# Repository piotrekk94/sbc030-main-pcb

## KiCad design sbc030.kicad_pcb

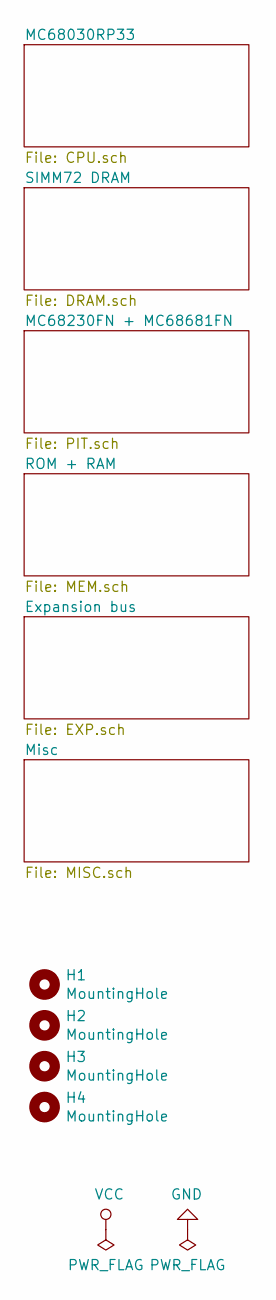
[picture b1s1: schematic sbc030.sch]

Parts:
H1, H2, H3, H4: MountingHole; MountingHole_3.2mm_M3_Pad

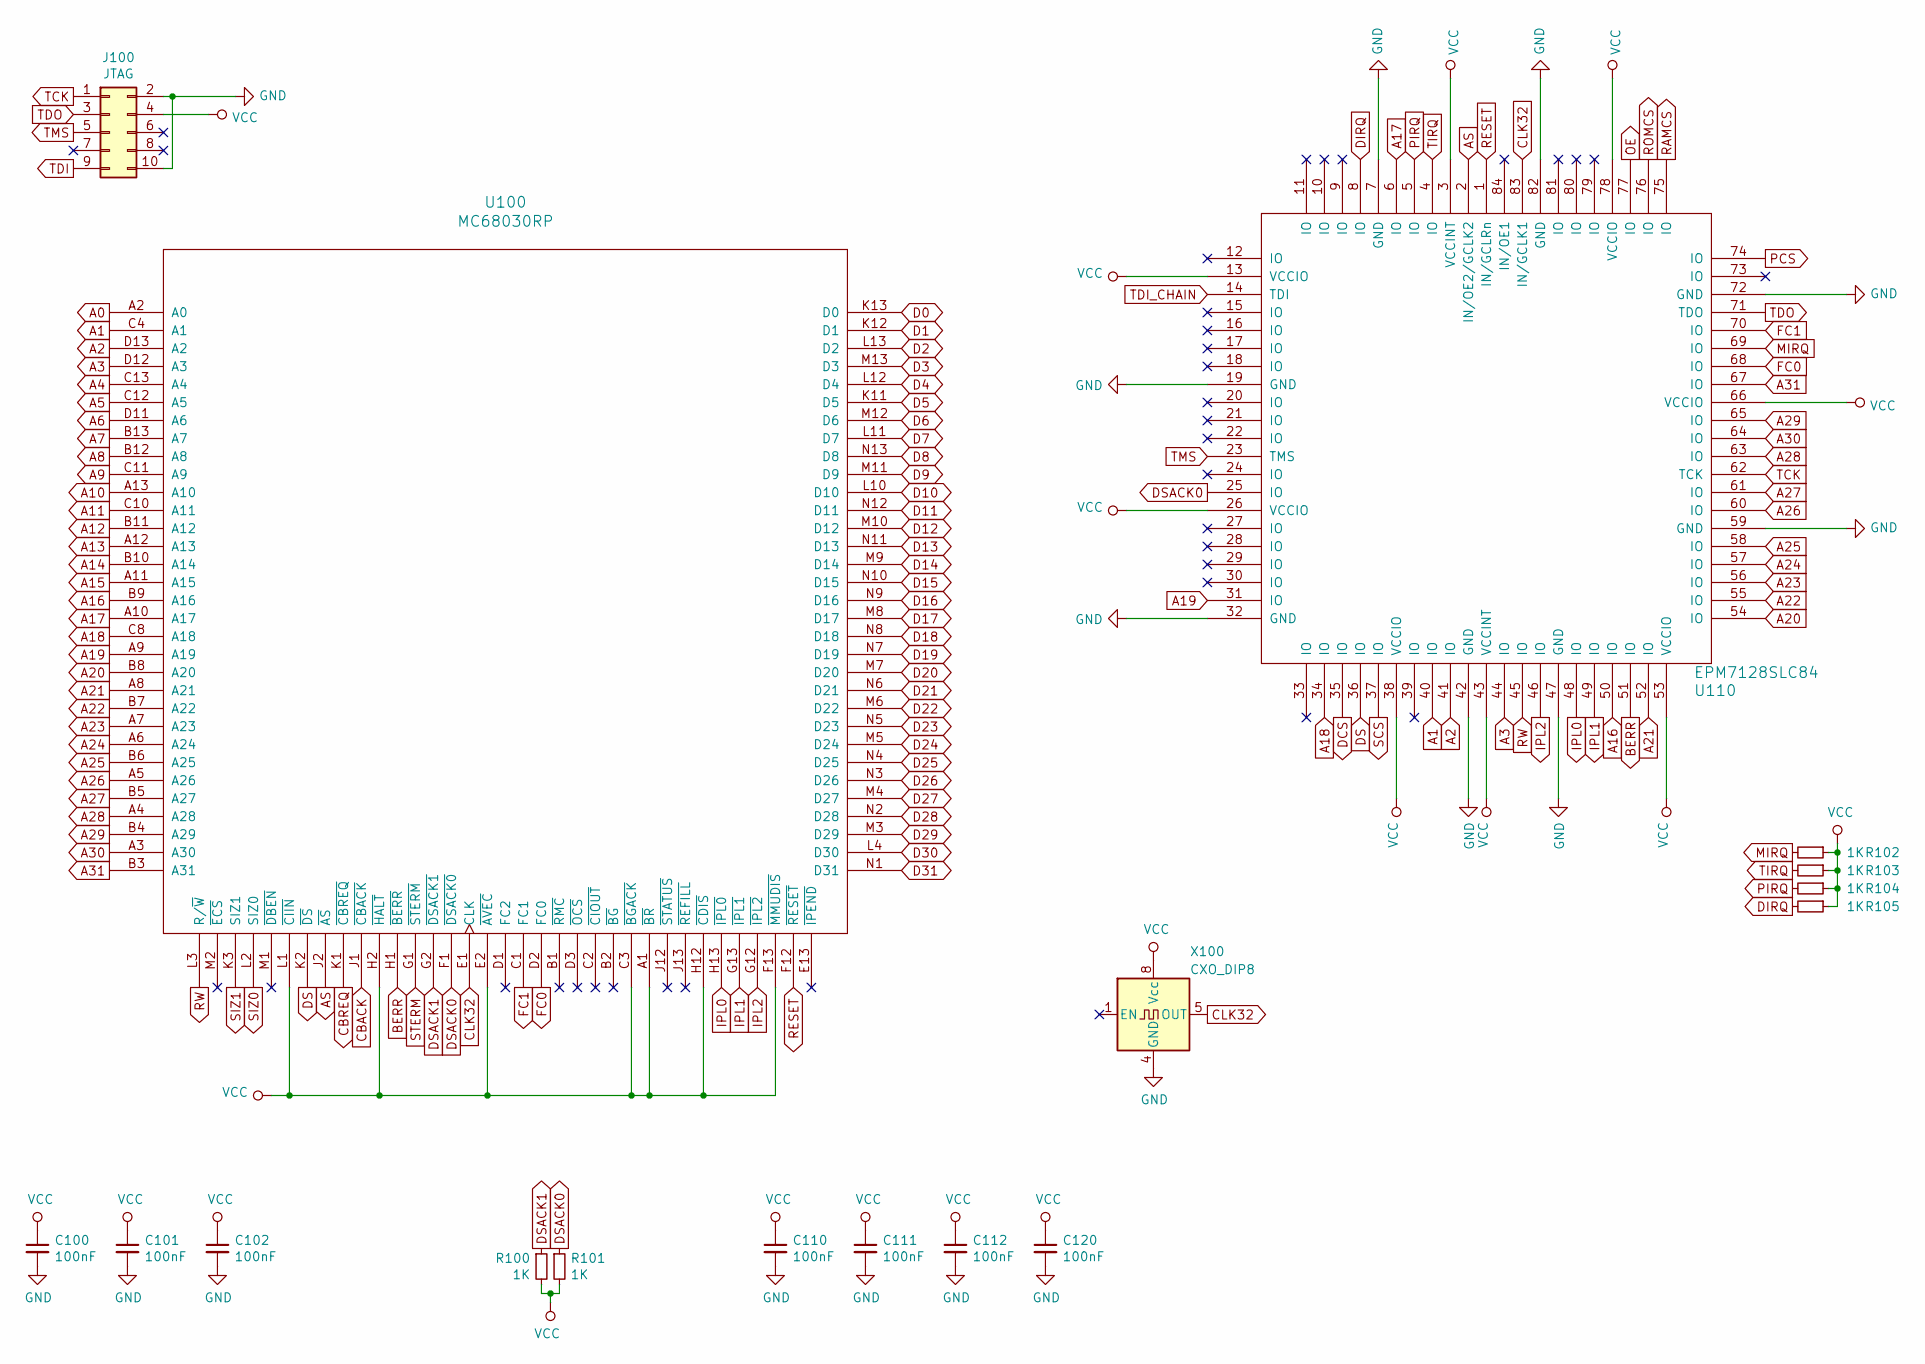
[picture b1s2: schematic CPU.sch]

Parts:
C100, C101, C102, C110, C111, C112, C120: 100nF; C_0603_1608Metric_Pad1.05x0.95mm_HandSolder
J100: JTAG; PinHeader_2x05_P2.54mm_Vertical
R100, R101, R102, R103, R104, R105: 1K; R_0603_1608Metric_Pad1.05x0.95mm_HandSolder
U100: MC68030RP; PGA128
U110: EPM7128SLC84; PLCC-84_THT-Socket
X100: CXO_DIP8; Oscillator_DIP-8

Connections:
A0: U100.A2 (A0); also elsewhere on the board
A1: U100.C4 (A1), U110.40 (IO); also elsewhere on the board
A2: U100.D13 (A2), U110.41 (IO); also elsewhere on the board
A3: U100.D12 (A3), U110.44 (IO); also elsewhere on the board
A4: U100.C13 (A4); also elsewhere on the board
A5: U100.C12 (A5); also elsewhere on the board
A6: U100.D11 (A6); also elsewhere on the board
A7: U100.B13 (A7); also elsewhere on the board
A8: U100.B12 (A8); also elsewhere on the board
A9: U100.C11 (A9); also elsewhere on the board
A10: U100.A13 (A10); also elsewhere on the board
A11: U100.C10 (A11); also elsewhere on the board
A12: U100.B11 (A12); also elsewhere on the board
A13: U100.A12 (A13); also elsewhere on the board
A14: U100.B10 (A14); also elsewhere on the board
A15: U100.A11 (A15); also elsewhere on the board
A16: U100.B9 (A16), U110.50 (IO); also elsewhere on the board
A17: U100.A10 (A17), U110.6 (IO); also elsewhere on the board
A18: U100.C8 (A18), U110.34 (IO); also elsewhere on the board
A19: U100.A9 (A19), U110.31 (IO); also elsewhere on the board
A20: U100.B8 (A20), U110.54 (IO); also elsewhere on the board
A21: U100.A8 (A21), U110.52 (IO); also elsewhere on the board
A22: U100.B7 (A22), U110.55 (IO); also elsewhere on the board
A23: U100.A7 (A23), U110.56 (IO); also elsewhere on the board
A24: U100.A6 (A24), U110.57 (IO); also elsewhere on the board
A25: U100.B6 (A25), U110.58 (IO); also elsewhere on the board
A26: U100.A5 (A26), U110.60 (IO); also elsewhere on the board
A27: U100.B5 (A27), U110.61 (IO); also elsewhere on the board
A28: U100.A4 (A28), U110.63 (IO); also elsewhere on the board
A29: U100.B4 (A29), U110.65 (IO); also elsewhere on the board
A30: U100.A3 (A30), U110.64 (IO); also elsewhere on the board
A31: U100.B3 (A31), U110.67 (IO); also elsewhere on the board
AS: U100.J2 (~AS), U110.2 (IN/OE2/GCLK2); also elsewhere on the board
BERR: U100.H1 (~BERR), U110.51 (IO)
CBACK: U100.J1 (~CBACK); also elsewhere on the board
CBREQ: U100.K1 (~CBREQ); also elsewhere on the board
CLK32: U100.E1 (CLK), U110.83 (IN/GCLK1), X100.5 (OUT); also elsewhere on the board
D0: U100.K13 (D0); also elsewhere on the board
D1: U100.K12 (D1); also elsewhere on the board
D2: U100.L13 (D2); also elsewhere on the board
D3: U100.M13 (D3); also elsewhere on the board
D4: U100.L12 (D4); also elsewhere on the board
D5: U100.K11 (D5); also elsewhere on the board
D6: U100.M12 (D6); also elsewhere on the board
D7: U100.L11 (D7); also elsewhere on the board
D8: U100.N13 (D8); also elsewhere on the board
D9: U100.M11 (D9); also elsewhere on the board
D10: U100.L10 (D10); also elsewhere on the board
D11: U100.N12 (D11); also elsewhere on the board
D12: U100.M10 (D12); also elsewhere on the board
D13: U100.N11 (D13); also elsewhere on the board
D14: U100.M9 (D14); also elsewhere on the board
D15: U100.N10 (D15); also elsewhere on the board
D16: U100.N9 (D16); also elsewhere on the board
D17: U100.M8 (D17); also elsewhere on the board
D18: U100.N8 (D18); also elsewhere on the board
D19: U100.N7 (D19); also elsewhere on the board
D20: U100.M7 (D20); also elsewhere on the board
D21: U100.N6 (D21); also elsewhere on the board
D22: U100.M6 (D22); also elsewhere on the board
D23: U100.N5 (D23); also elsewhere on the board
D24: U100.M5 (D24); also elsewhere on the board
D25: U100.N4 (D25); also elsewhere on the board
D26: U100.N3 (D26); also elsewhere on the board
D27: U100.M4 (D27); also elsewhere on the board
D28: U100.N2 (D28); also elsewhere on the board
D29: U100.M3 (D29); also elsewhere on the board
D30: U100.L4 (D30); also elsewhere on the board
D31: U100.N1 (D31); also elsewhere on the board
DCS: U110.35 (IO); also elsewhere on the board
DIRQ: R105.2, U110.8 (IO); also elsewhere on the board
DS: U100.K2 (~DS), U110.36 (IO); also elsewhere on the board
DSACK0: R101.1, U100.F1 (~DSACK0), U110.25 (IO); also elsewhere on the board
DSACK1: R100.1, U100.G2 (~DSACK1); also elsewhere on the board
FC0: U100.D2 (FC0), U110.68 (IO); also elsewhere on the board
FC1: U100.C1 (FC1), U110.70 (IO); also elsewhere on the board
GND: C100.2, C101.2, C102.2, C110.2, C111.2, C112.2, C120.2, J100.2, J100.10, U100.C5 (GND), U100.C7 (GND), U100.C9 (GND), U100.E3 (GND), U100.E11 (GND), U100.F3 (GND), U100.G3 (GND), U100.G11 (GND), U100.J3 (GND), U100.J11 (GND), U100.L5 (GND), U100.L7 (GND), U100.L8 (GND), U100.L9 (GND), U110.7 (GND), U110.19 (GND), U110.32 (GND), U110.42 (GND), U110.47 (GND), U110.59 (GND), U110.72 (GND), U110.82 (GND), X100.4 (GND); also elsewhere on the board
IPL0: U100.H13 (~IPL0), U110.48 (IO)
IPL1: U100.G13 (~IPL1), U110.49 (IO)
IPL2: U100.G12 (~IPL2), U110.46 (IO)
MIRQ: R102.2, U110.69 (IO); also elsewhere on the board
OE: U110.77 (IO); also elsewhere on the board
PCS: U110.74 (IO); also elsewhere on the board
PIRQ: R104.2, U110.5 (IO); also elsewhere on the board
RAMCS: U110.75 (IO); also elsewhere on the board
RESET: U100.F12 (~RESET), U110.1 (IN/GCLRn); also elsewhere on the board
ROMCS: U110.76 (IO); also elsewhere on the board
RW: U100.L3 (R/~W), U110.45 (IO); also elsewhere on the board
SCS: U110.37 (IO); also elsewhere on the board
SIZ0: U100.L2 (SIZ0); also elsewhere on the board
SIZ1: U100.K3 (SIZ1); also elsewhere on the board
STERM: U100.G1 (~STERM); also elsewhere on the board
TCK: J100.1, U110.62 (TCK); also elsewhere on the board
TDI: J100.9; also elsewhere on the board
TDI_CHAIN: U110.14 (TDI); also elsewhere on the board
TDO: J100.3, U110.71 (TDO)
TIRQ: R103.2, U110.4 (IO); also elsewhere on the board
TMS: J100.5, U110.23 (TMS); also elsewhere on the board
VCC: C100.1, C101.1, C102.1, C110.1, C111.1, C112.1, C120.1, J100.4, R100.2, R101.2, R102.1, R103.1, R104.1, R105.1, U100.A1 (~BR), U100.C3 (~BGACK), U100.C6 (VCC), U100.D4 (VCC), U100.D10 (VCC), U100.E2 (~AVEC), U100.F2 (VCC), U100.F11 (VCC), U100.F13 (~MMUDIS), U100.H2 (~HALT), U100.H3 (VCC), U100.H11 (VCC), U100.H12 (~CDIS), U100.K4 (VCC), U100.K10 (VCC), U100.L1 (~CIIN), U100.L6 (VCC), U110.3 (VCCINT), U110.13 (VCCIO), U110.26 (VCCIO), U110.38 (VCCIO), U110.43 (VCCINT), U110.53 (VCCIO), U110.66 (VCCIO), U110.78 (VCCIO), X100.8 (Vcc); also elsewhere on the board

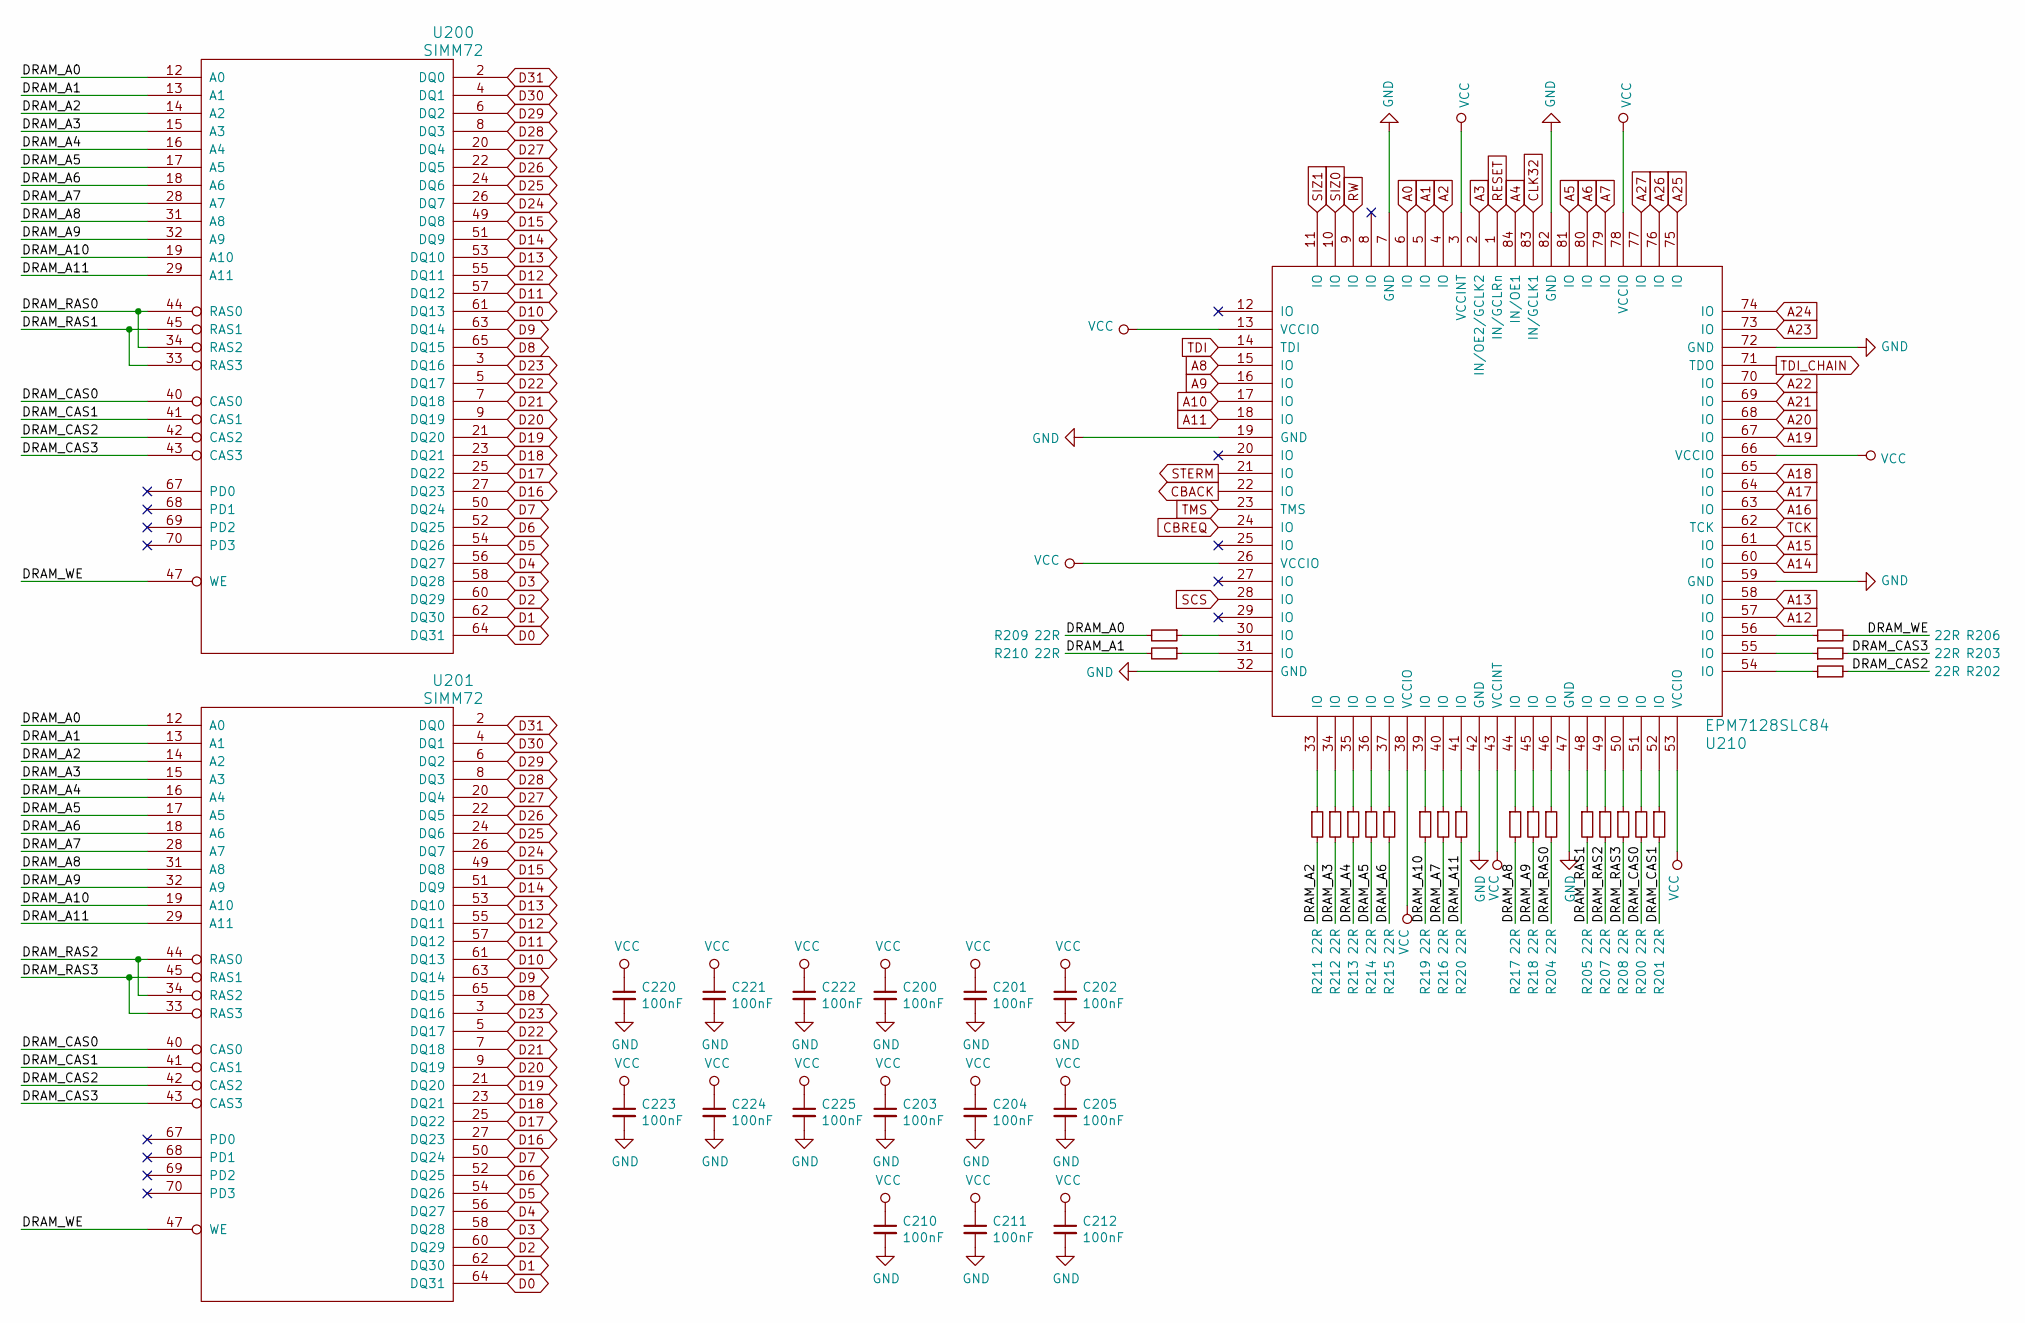
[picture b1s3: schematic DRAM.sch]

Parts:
C200, C201, C202, C203, C204, C205, C210, C211, C212, C220, C221, C222, C223, C224, C225: 100nF; C_0603_1608Metric_Pad1.05x0.95mm_HandSolder
R200, R201, R202, R203, R204, R205, R206, R207, R208, R209, R210, R211, R212, R213, R214, R215, R216, R217, R218, R219, R220: 22R; R_0603_1608Metric_Pad1.05x0.95mm_HandSolder
U200, U201: SIMM72; SIM72
U210: EPM7128SLC84; PLCC-84_THT-Socket

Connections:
/SIMM72 DRAM/DRAM_A0: R209.2, U200.12 (A0), U201.12 (A0)
/SIMM72 DRAM/DRAM_A1: R210.2, U200.13 (A1), U201.13 (A1)
/SIMM72 DRAM/DRAM_A2: R211.2, U200.14 (A2), U201.14 (A2)
/SIMM72 DRAM/DRAM_A3: R212.2, U200.15 (A3), U201.15 (A3)
/SIMM72 DRAM/DRAM_A4: R213.2, U200.16 (A4), U201.16 (A4)
/SIMM72 DRAM/DRAM_A5: R214.2, U200.17 (A5), U201.17 (A5)
/SIMM72 DRAM/DRAM_A6: R215.2, U200.18 (A6), U201.18 (A6)
/SIMM72 DRAM/DRAM_A7: R216.2, U200.28 (A7), U201.28 (A7)
/SIMM72 DRAM/DRAM_A8: R217.2, U200.31 (A8), U201.31 (A8)
/SIMM72 DRAM/DRAM_A9: R218.2, U200.32 (A9), U201.32 (A9)
/SIMM72 DRAM/DRAM_A10: R219.2, U200.19 (A10), U201.19 (A10)
/SIMM72 DRAM/DRAM_A11: R220.2, U200.29 (A11), U201.29 (A11)
/SIMM72 DRAM/DRAM_CAS0: R200.2, U200.40 (CAS0), U201.40 (CAS0)
/SIMM72 DRAM/DRAM_CAS1: R201.2, U200.41 (CAS1), U201.41 (CAS1)
/SIMM72 DRAM/DRAM_CAS2: R202.2, U200.42 (CAS2), U201.42 (CAS2)
/SIMM72 DRAM/DRAM_CAS3: R203.2, U200.43 (CAS3), U201.43 (CAS3)
/SIMM72 DRAM/DRAM_RAS0: R204.2, U200.34 (RAS2), U200.44 (RAS0)
/SIMM72 DRAM/DRAM_RAS1: R205.2, U200.33 (RAS3), U200.45 (RAS1)
/SIMM72 DRAM/DRAM_RAS2: R207.2, U201.34 (RAS2), U201.44 (RAS0)
/SIMM72 DRAM/DRAM_RAS3: R208.2, U201.33 (RAS3), U201.45 (RAS1)
/SIMM72 DRAM/DRAM_WE: R206.2, U200.47 (WE), U201.47 (WE)
A0: U210.6 (IO); also elsewhere on the board
A1: U210.5 (IO); also elsewhere on the board
A2: U210.4 (IO); also elsewhere on the board
A3: U210.2 (IN/OE2/GCLK2); also elsewhere on the board
A4: U210.84 (IN/OE1); also elsewhere on the board
A5: U210.81 (IO); also elsewhere on the board
A6: U210.80 (IO); also elsewhere on the board
A7: U210.79 (IO); also elsewhere on the board
A8: U210.15 (IO); also elsewhere on the board
A9: U210.16 (IO); also elsewhere on the board
A10: U210.17 (IO); also elsewhere on the board
A11: U210.18 (IO); also elsewhere on the board
A12: U210.57 (IO); also elsewhere on the board
A13: U210.58 (IO); also elsewhere on the board
A14: U210.60 (IO); also elsewhere on the board
A15: U210.61 (IO); also elsewhere on the board
A16: U210.63 (IO); also elsewhere on the board
A17: U210.64 (IO); also elsewhere on the board
A18: U210.65 (IO); also elsewhere on the board
A19: U210.67 (IO); also elsewhere on the board
A20: U210.68 (IO); also elsewhere on the board
A21: U210.69 (IO); also elsewhere on the board
A22: U210.70 (IO); also elsewhere on the board
A23: U210.73 (IO); also elsewhere on the board
A24: U210.74 (IO); also elsewhere on the board
A25: U210.75 (IO); also elsewhere on the board
A26: U210.76 (IO); also elsewhere on the board
A27: U210.77 (IO); also elsewhere on the board
CBACK: U210.22 (IO); also elsewhere on the board
CBREQ: U210.24 (IO); also elsewhere on the board
CLK32: U210.83 (IN/GCLK1); also elsewhere on the board
D0: U200.64 (DQ31), U201.64 (DQ31); also elsewhere on the board
D1: U200.62 (DQ30), U201.62 (DQ30); also elsewhere on the board
D2: U200.60 (DQ29), U201.60 (DQ29); also elsewhere on the board
D3: U200.58 (DQ28), U201.58 (DQ28); also elsewhere on the board
D4: U200.56 (DQ27), U201.56 (DQ27); also elsewhere on the board
D5: U200.54 (DQ26), U201.54 (DQ26); also elsewhere on the board
D6: U200.52 (DQ25), U201.52 (DQ25); also elsewhere on the board
D7: U200.50 (DQ24), U201.50 (DQ24); also elsewhere on the board
D8: U200.65 (DQ15), U201.65 (DQ15); also elsewhere on the board
D9: U200.63 (DQ14), U201.63 (DQ14); also elsewhere on the board
D10: U200.61 (DQ13), U201.61 (DQ13); also elsewhere on the board
D11: U200.57 (DQ12), U201.57 (DQ12); also elsewhere on the board
D12: U200.55 (DQ11), U201.55 (DQ11); also elsewhere on the board
D13: U200.53 (DQ10), U201.53 (DQ10); also elsewhere on the board
D14: U200.51 (DQ9), U201.51 (DQ9); also elsewhere on the board
D15: U200.49 (DQ8), U201.49 (DQ8); also elsewhere on the board
D16: U200.27 (DQ23), U201.27 (DQ23); also elsewhere on the board
D17: U200.25 (DQ22), U201.25 (DQ22); also elsewhere on the board
D18: U200.23 (DQ21), U201.23 (DQ21); also elsewhere on the board
D19: U200.21 (DQ20), U201.21 (DQ20); also elsewhere on the board
D20: U200.9 (DQ19), U201.9 (DQ19); also elsewhere on the board
D21: U200.7 (DQ18), U201.7 (DQ18); also elsewhere on the board
D22: U200.5 (DQ17), U201.5 (DQ17); also elsewhere on the board
D23: U200.3 (DQ16), U201.3 (DQ16); also elsewhere on the board
D24: U200.26 (DQ7), U201.26 (DQ7); also elsewhere on the board
D25: U200.24 (DQ6), U201.24 (DQ6); also elsewhere on the board
D26: U200.22 (DQ5), U201.22 (DQ5); also elsewhere on the board
D27: U200.20 (DQ4), U201.20 (DQ4); also elsewhere on the board
D28: U200.8 (DQ3), U201.8 (DQ3); also elsewhere on the board
D29: U200.6 (DQ2), U201.6 (DQ2); also elsewhere on the board
D30: U200.4 (DQ1), U201.4 (DQ1); also elsewhere on the board
D31: U200.2 (DQ0), U201.2 (DQ0); also elsewhere on the board
GND: C200.2, C201.2, C202.2, C203.2, C204.2, C205.2, C210.2, C211.2, C212.2, C220.2, C221.2, C222.2, C223.2, C224.2, C225.2, U200.1 (GND), U200.39 (GND), U200.72 (GND), U201.1 (GND), U201.39 (GND), U201.72 (GND), U210.7 (GND), U210.19 (GND), U210.32 (GND), U210.42 (GND), U210.47 (GND), U210.59 (GND), U210.72 (GND), U210.82 (GND); also elsewhere on the board
unnamed: R200.1, U210.51 (IO)
unnamed: R201.1, U210.52 (IO)
unnamed: R202.1, U210.54 (IO)
unnamed: R203.1, U210.55 (IO)
unnamed: R204.1, U210.46 (IO)
unnamed: R205.1, U210.48 (IO)
unnamed: R206.1, U210.56 (IO)
unnamed: R207.1, U210.49 (IO)
unnamed: R208.1, U210.50 (IO)
unnamed: R209.1, U210.30 (IO)
unnamed: R210.1, U210.31 (IO)
unnamed: R211.1, U210.33 (IO)
unnamed: R212.1, U210.34 (IO)
unnamed: R213.1, U210.35 (IO)
unnamed: R214.1, U210.36 (IO)
unnamed: R215.1, U210.37 (IO)
unnamed: R216.1, U210.40 (IO)
unnamed: R217.1, U210.44 (IO)
unnamed: R218.1, U210.45 (IO)
unnamed: R219.1, U210.39 (IO)
unnamed: R220.1, U210.41 (IO)
RESET: U210.1 (IN/GCLRn); also elsewhere on the board
RW: U210.9 (IO); also elsewhere on the board
SCS: U210.28 (IO); also elsewhere on the board
SIZ0: U210.10 (IO); also elsewhere on the board
SIZ1: U210.11 (IO); also elsewhere on the board
STERM: U210.21 (IO); also elsewhere on the board
TCK: U210.62 (TCK); also elsewhere on the board
TDI: U210.14 (TDI); also elsewhere on the board
TDI_CHAIN: U210.71 (TDO); also elsewhere on the board
TMS: U210.23 (TMS); also elsewhere on the board
VCC: C200.1, C201.1, C202.1, C203.1, C204.1, C205.1, C210.1, C211.1, C212.1, C220.1, C221.1, C222.1, C223.1, C224.1, C225.1, U200.10 (VCC), U200.30 (VCC), U200.59 (VCC), U201.10 (VCC), U201.30 (VCC), U201.59 (VCC), U210.3 (VCCINT), U210.13 (VCCIO), U210.26 (VCCIO), U210.38 (VCCIO), U210.43 (VCCINT), U210.53 (VCCIO), U210.66 (VCCIO), U210.78 (VCCIO); also elsewhere on the board

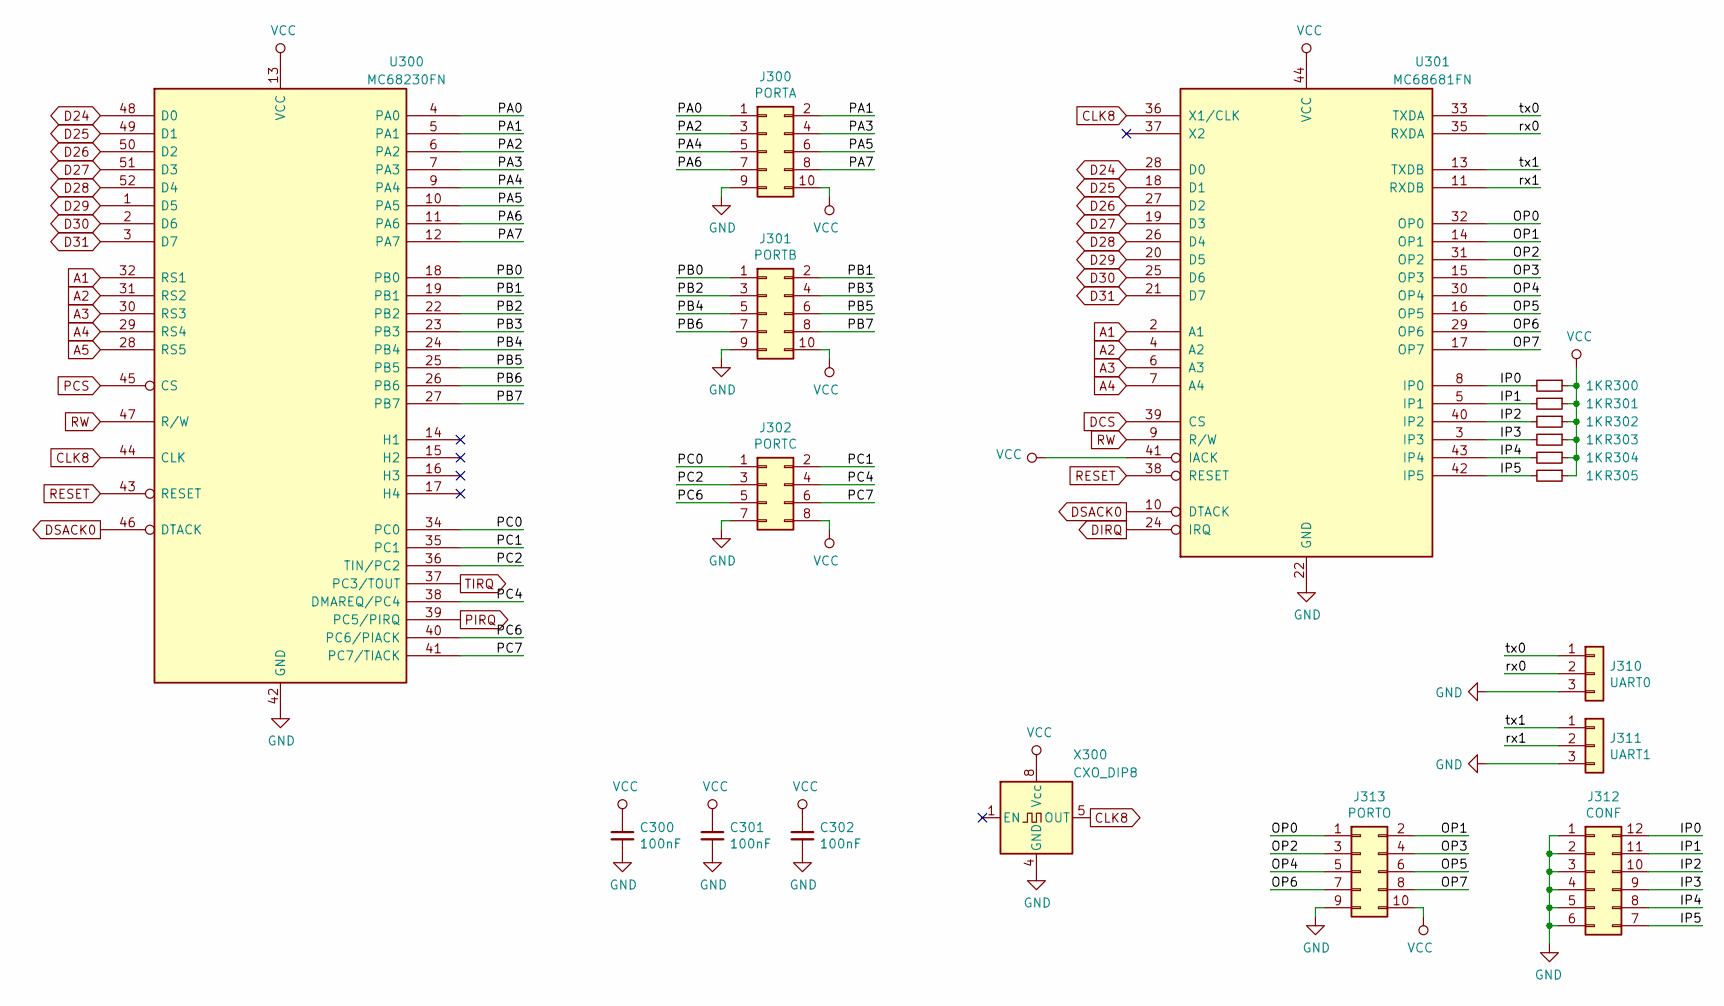
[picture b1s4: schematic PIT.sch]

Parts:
C300, C301, C302: 100nF; C_0603_1608Metric_Pad1.05x0.95mm_HandSolder
J300: PORTA; PinHeader_2x05_P2.54mm_Vertical
J301: PORTB; PinHeader_2x05_P2.54mm_Vertical
J302: PORTC; PinHeader_2x04_P2.54mm_Vertical
J310: UART0; PinHeader_1x03_P2.54mm_Vertical
J311: UART1; PinHeader_1x03_P2.54mm_Vertical
J312: CONF; DIP-12_W7.62mm
J313: PORTO; PinHeader_2x05_P2.54mm_Vertical
R300, R301, R302, R303, R304, R305: 1K; R_0603_1608Metric_Pad1.05x0.95mm_HandSolder
U300: MC68230FN; PLCC-52_THT-Socket
U301: MC68681FN; PLCC-44_THT-Socket
X300: CXO_DIP8; Oscillator_DIP-8

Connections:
/MC68230FN + MC68681FN/IP0: J312.12, R300.2, U301.8 (IP0)
/MC68230FN + MC68681FN/IP1: J312.11, R301.2, U301.5 (IP1)
/MC68230FN + MC68681FN/IP2: J312.10, R302.2, U301.40 (IP2)
/MC68230FN + MC68681FN/IP3: J312.9, R303.2, U301.3 (IP3)
/MC68230FN + MC68681FN/IP4: J312.8, R304.2, U301.43 (IP4)
/MC68230FN + MC68681FN/IP5: J312.7, R305.2, U301.42 (IP5)
/MC68230FN + MC68681FN/OP0: J313.1, U301.32 (OP0)
/MC68230FN + MC68681FN/OP1: J313.2, U301.14 (OP1)
/MC68230FN + MC68681FN/OP2: J313.3, U301.31 (OP2)
/MC68230FN + MC68681FN/OP3: J313.4, U301.15 (OP3)
/MC68230FN + MC68681FN/OP4: J313.5, U301.30 (OP4)
/MC68230FN + MC68681FN/OP5: J313.6, U301.16 (OP5)
/MC68230FN + MC68681FN/OP6: J313.7, U301.29 (OP6)
/MC68230FN + MC68681FN/OP7: J313.8, U301.17 (OP7)
/MC68230FN + MC68681FN/PA0: J300.1, U300.4 (PA0)
/MC68230FN + MC68681FN/PA1: J300.2, U300.5 (PA1)
/MC68230FN + MC68681FN/PA2: J300.3, U300.6 (PA2)
/MC68230FN + MC68681FN/PA3: J300.4, U300.7 (PA3)
/MC68230FN + MC68681FN/PA4: J300.5, U300.9 (PA4)
/MC68230FN + MC68681FN/PA5: J300.6, U300.10 (PA5)
/MC68230FN + MC68681FN/PA6: J300.7, U300.11 (PA6)
/MC68230FN + MC68681FN/PA7: J300.8, U300.12 (PA7)
/MC68230FN + MC68681FN/PB0: J301.1, U300.18 (PB0)
/MC68230FN + MC68681FN/PB1: J301.2, U300.19 (PB1)
/MC68230FN + MC68681FN/PB2: J301.3, U300.22 (PB2)
/MC68230FN + MC68681FN/PB3: J301.4, U300.23 (PB3)
/MC68230FN + MC68681FN/PB4: J301.5, U300.24 (PB4)
/MC68230FN + MC68681FN/PB5: J301.6, U300.25 (PB5)
/MC68230FN + MC68681FN/PB6: J301.7, U300.26 (PB6)
/MC68230FN + MC68681FN/PB7: J301.8, U300.27 (PB7)
/MC68230FN + MC68681FN/PC0: J302.1, U300.34 (PC0)
/MC68230FN + MC68681FN/PC1: J302.2, U300.35 (PC1)
/MC68230FN + MC68681FN/PC2: J302.3, U300.36 (TIN/PC2)
/MC68230FN + MC68681FN/PC4: J302.4, U300.38 (DMAREQ/PC4)
/MC68230FN + MC68681FN/PC6: J302.5, U300.40 (PC6/PIACK)
/MC68230FN + MC68681FN/PC7: J302.6, U300.41 (PC7/TIACK)
/MC68230FN + MC68681FN/rx0: J310.2, U301.35 (RXDA)
/MC68230FN + MC68681FN/rx1: J311.2, U301.11 (RXDB)
/MC68230FN + MC68681FN/tx0: J310.1, U301.33 (TXDA)
/MC68230FN + MC68681FN/tx1: J311.1, U301.13 (TXDB)
A1: U300.32 (RS1), U301.2 (A1); also elsewhere on the board
A2: U300.31 (RS2), U301.4 (A2); also elsewhere on the board
A3: U300.30 (RS3), U301.6 (A3); also elsewhere on the board
A4: U300.29 (RS4), U301.7 (A4); also elsewhere on the board
A5: U300.28 (RS5); also elsewhere on the board
CLK8: U300.44 (CLK), U301.36 (X1/CLK), X300.5 (OUT)
D24: U300.48 (D0), U301.28 (D0); also elsewhere on the board
D25: U300.49 (D1), U301.18 (D1); also elsewhere on the board
D26: U300.50 (D2), U301.27 (D2); also elsewhere on the board
D27: U300.51 (D3), U301.19 (D3); also elsewhere on the board
D28: U300.52 (D4), U301.26 (D4); also elsewhere on the board
D29: U300.1 (D5), U301.20 (D5); also elsewhere on the board
D30: U300.2 (D6), U301.25 (D6); also elsewhere on the board
D31: U300.3 (D7), U301.21 (D7); also elsewhere on the board
DCS: U301.39 (CS); also elsewhere on the board
DIRQ: U301.24 (IRQ); also elsewhere on the board
DSACK0: U300.46 (DTACK), U301.10 (DTACK); also elsewhere on the board
GND: C300.2, C301.2, C302.2, J300.9, J301.9, J302.7, J310.3, J311.3, J312.1, J312.2, J312.3, J312.4, J312.5, J312.6, J313.9, U300.42 (GND), U301.22 (GND), X300.4 (GND); also elsewhere on the board
PCS: U300.45 (CS); also elsewhere on the board
PIRQ: U300.39 (PC5/PIRQ); also elsewhere on the board
RESET: U300.43 (RESET), U301.38 (RESET); also elsewhere on the board
RW: U300.47 (R/W), U301.9 (R/W); also elsewhere on the board
TIRQ: U300.37 (PC3/TOUT); also elsewhere on the board
VCC: C300.1, C301.1, C302.1, J300.10, J301.10, J302.8, J313.10, R300.1, R301.1, R302.1, R303.1, R304.1, R305.1, U300.13 (VCC), U301.41 (IACK), U301.44 (VCC), X300.8 (Vcc); also elsewhere on the board

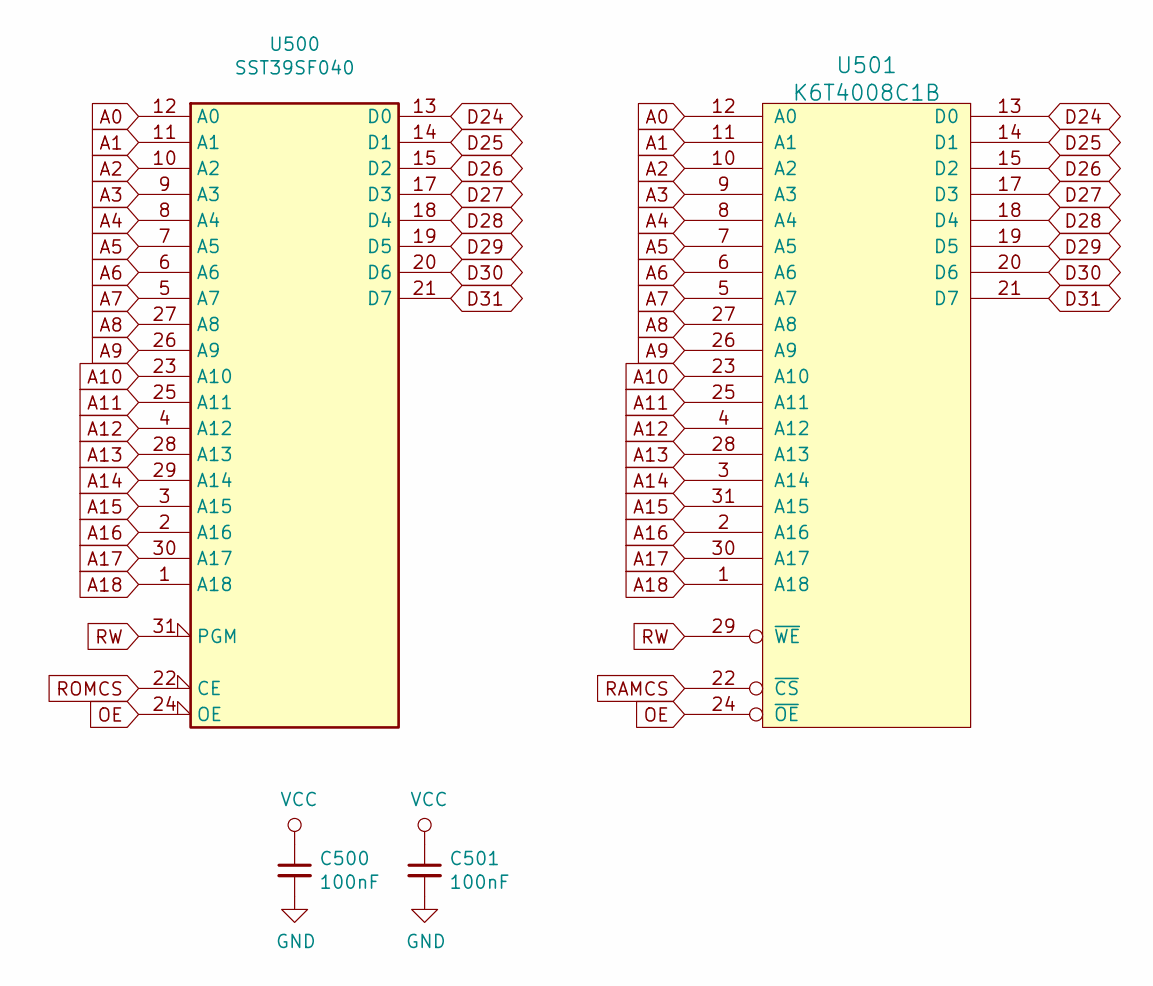
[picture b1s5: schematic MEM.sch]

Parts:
C500, C501: 100nF; C_0603_1608Metric_Pad1.05x0.95mm_HandSolder
U500: SST39SF040; DIP-32_W15.24mm
U501: K6T4008C1B; DIP-32_W15.24mm

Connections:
A0: U500.12 (A0), U501.12 (A0); also elsewhere on the board
A1: U500.11 (A1), U501.11 (A1); also elsewhere on the board
A2: U500.10 (A2), U501.10 (A2); also elsewhere on the board
A3: U500.9 (A3), U501.9 (A3); also elsewhere on the board
A4: U500.8 (A4), U501.8 (A4); also elsewhere on the board
A5: U500.7 (A5), U501.7 (A5); also elsewhere on the board
A6: U500.6 (A6), U501.6 (A6); also elsewhere on the board
A7: U500.5 (A7), U501.5 (A7); also elsewhere on the board
A8: U500.27 (A8), U501.27 (A8); also elsewhere on the board
A9: U500.26 (A9), U501.26 (A9); also elsewhere on the board
A10: U500.23 (A10), U501.23 (A10); also elsewhere on the board
A11: U500.25 (A11), U501.25 (A11); also elsewhere on the board
A12: U500.4 (A12), U501.4 (A12); also elsewhere on the board
A13: U500.28 (A13), U501.28 (A13); also elsewhere on the board
A14: U500.29 (A14), U501.3 (A14); also elsewhere on the board
A15: U500.3 (A15), U501.31 (A15); also elsewhere on the board
A16: U500.2 (A16), U501.2 (A16); also elsewhere on the board
A17: U500.30 (A17), U501.30 (A17); also elsewhere on the board
A18: U500.1 (A18), U501.1 (A18); also elsewhere on the board
D24: U500.13 (D0), U501.13 (D0); also elsewhere on the board
D25: U500.14 (D1), U501.14 (D1); also elsewhere on the board
D26: U500.15 (D2), U501.15 (D2); also elsewhere on the board
D27: U500.17 (D3), U501.17 (D3); also elsewhere on the board
D28: U500.18 (D4), U501.18 (D4); also elsewhere on the board
D29: U500.19 (D5), U501.19 (D5); also elsewhere on the board
D30: U500.20 (D6), U501.20 (D6); also elsewhere on the board
D31: U500.21 (D7), U501.21 (D7); also elsewhere on the board
GND: C500.2, C501.2, U500.16 (GND), U501.16 (GND); also elsewhere on the board
OE: U500.24 (OE), U501.24 (~OE); also elsewhere on the board
RAMCS: U501.22 (~CS); also elsewhere on the board
ROMCS: U500.22 (CE); also elsewhere on the board
RW: U500.31 (PGM), U501.29 (~WE); also elsewhere on the board
VCC: C500.1, C501.1, U500.32 (VCC), U501.32 (VCC); also elsewhere on the board
